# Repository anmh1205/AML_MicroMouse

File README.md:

# AML MicroMouse

An autonomous Micromouse robot built around an **STM32F407VET6** microcontroller and VL53L0X laser distance sensors, with firmware, PCB design files, maze-solving experiments, and simulator resources.

*Competition footage — [watch on YouTube](https://www.youtube.com/watch?v=a5xwwyJaq_M).*

## Project overview

In a Micromouse competition, a robot must explore an initially unknown maze, recognize walls, determine a route toward the goal, and execute that route accurately. This project brings together embedded sensing, motion control, route planning, custom electronics, and simulation in a single engineering workspace.

The repository includes STM32 firmware workspaces and supporting experiments rather than a single installation package. It also retains the hardware and simulation materials used during development.

## Technical scope

| Area | Repository contents |
| --- | --- |
| Controller | STM32F407VET6-based firmware project |
| Wall sensing | VL53L0X laser-ranging sensors |
| Firmware toolchain | STM32CubeIDE-compatible project metadata, STM32CubeMX `.ioc` configuration, and build files |
| Embedded software | Sensor acquisition, control code, and maze-navigation experiments |
| Simulation | Micromouse simulator materials and C examples |
| Electronics | PCB design assets and bill of materials |

## Exploring and building the firmware

Start with the STM32 project under `1. MicroMouse Code/0. MicroMouse - STM32F407VET6/PCB_V1`. That directory contains `.project`, `.cproject`, `PCB_V1.ioc`, source code, startup assembly, linker scripts, and other toolchain files.

For a first build:

1. Install an STM32 development toolchain compatible with the included project, such as STM32CubeIDE.
2. Import the `PCB_V1` project from the existing-project workflow.
3. Review the MCU configuration, compiler settings, external libraries, and selected build configuration.
4. Build for the intended hardware. Flash only after confirming connections, debugger settings, and motor safety.

Some directories contain generated `Debug/` or `build/` artifacts from earlier development. These are historical outputs, not evidence that the current project has been revalidated with recent toolchain versions.

## Repository guide

- [Examples](0.%20Example/) — source material and technical experiments.
- [Firmware and controller projects](1.%20MicroMouse%20Code/) — STM32 firmware, ESP32 remote experiments, and C tests.
- [PCB design](2.%20MicroMouse%20PCB/) — electronics project materials.
- [Mechanical drawings](4.%20Drawing/) — design and mechanical references.
- [Simulation resources](5.%20Simulator/) — Micromouse simulator and example code.
- [Bill of materials](Bill.xlsx) — component inventory reference.

## Development context

The repository captures the engineering process behind a competition robot, including intermediate experiments and physical design files. Several firmware and simulator resources coexist; they should not be assumed to represent one unified production release.

No repository-wide license is currently declared. Check the terms of bundled libraries and third-party simulator materials before reuse or redistribution.

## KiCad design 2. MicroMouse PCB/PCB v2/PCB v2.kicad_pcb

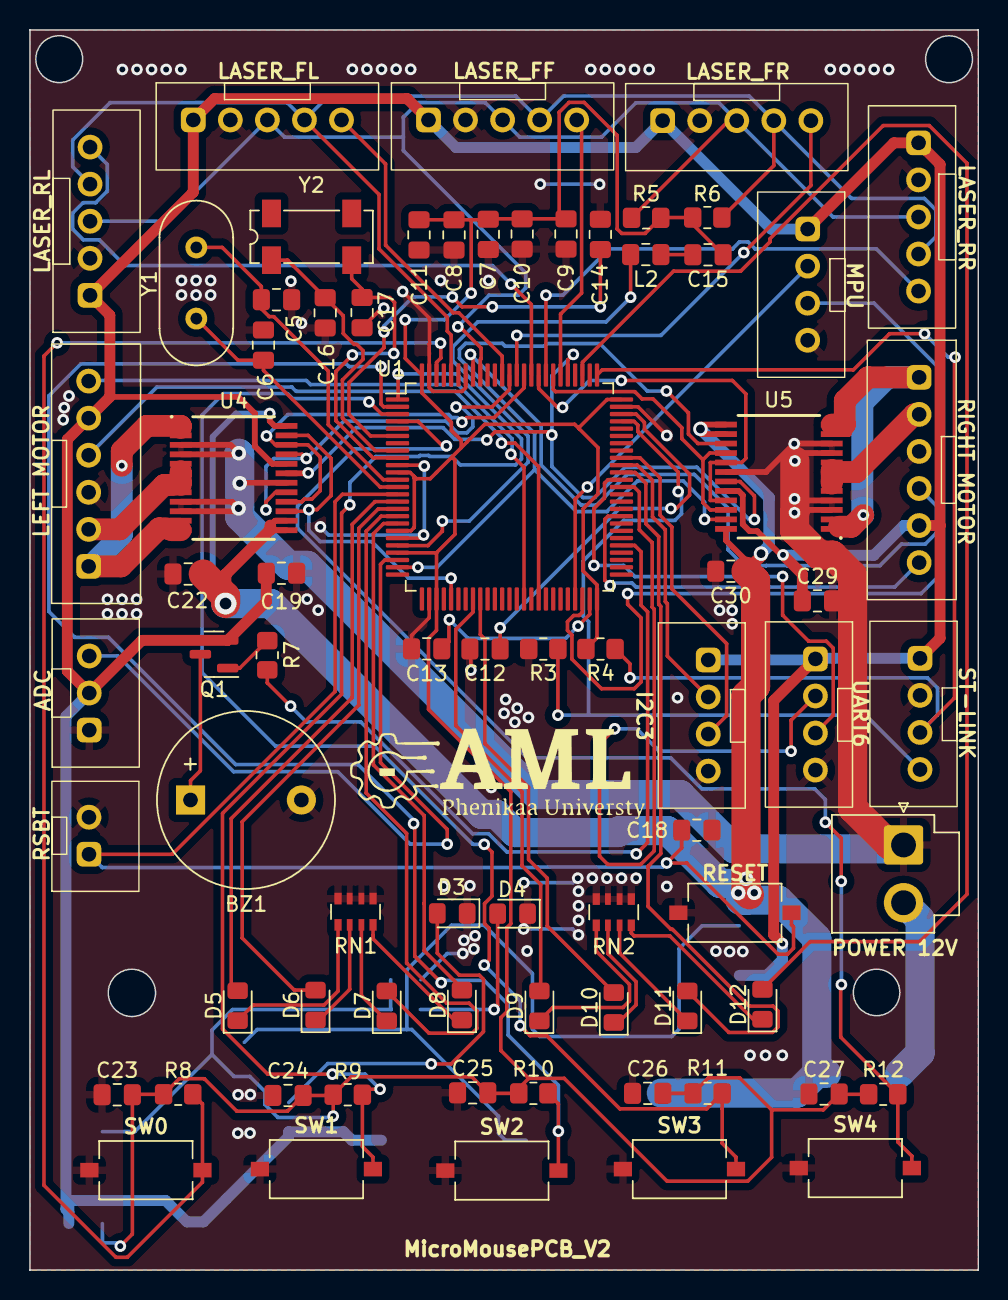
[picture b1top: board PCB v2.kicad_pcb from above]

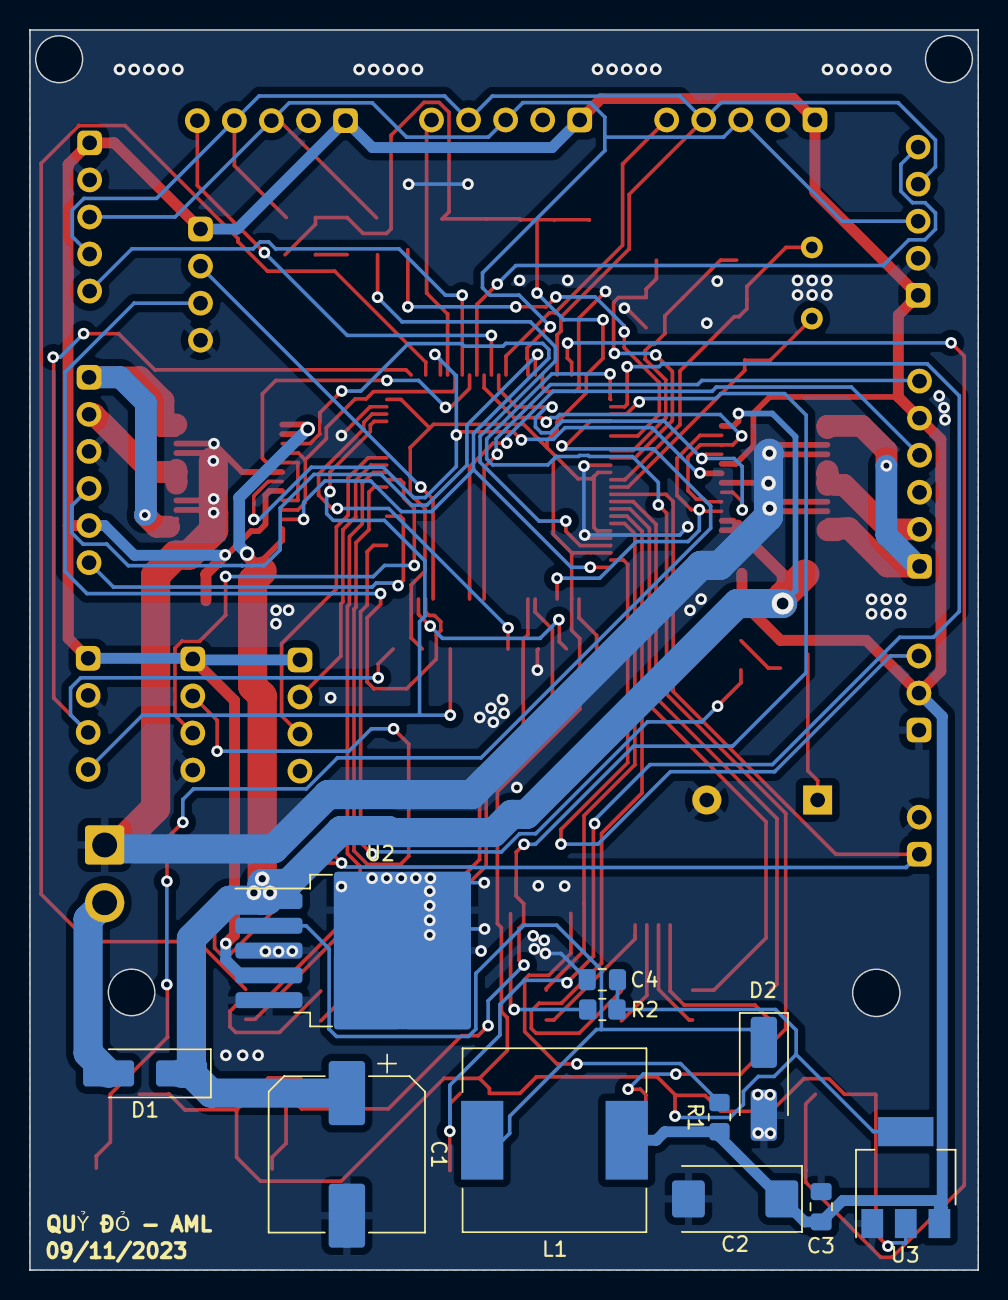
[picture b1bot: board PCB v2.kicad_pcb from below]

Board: 2 copper layers, 65.0 x 85.0 mm, 84 parts (11 on the bottom side), 73 nets.

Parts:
ADC: ADKEYBOARD; JST 3
BZ1: Buzzer; Buzzer_12x9.5RM7.6
C1: 680u; CP_Elec_10x10.5
C2: 220u; CP_EIA-7343-43_Kemet-X_Pad2.25x2.55mm_HandSolder
C3, C19, C22, C29, C30: 10U; C_0805_2012Metric_Pad1.18x1.45mm_HandSolder
C4: 47U; C_0805_2012Metric_Pad1.18x1.45mm_HandSolder
C5, C6, C16, C17: 20pF; C_0805_2012Metric_Pad1.18x1.45mm_HandSolder
C7, C8, C9, C10, C11, C12, C13, C14, C15, C18, C23, C24, C25, C26, C27: 100nF; C_0805_2012Metric_Pad1.18x1.45mm_HandSolder
D1, D2: 1N5822; D_SMA_Handsoldering
D3: 5VL; LED_0805_2012Metric_Pad1.15x1.40mm_HandSolder
D4, D5, D6, D7, D8, D9, D10, D11, D12: 3VL; LED_0805_2012Metric_Pad1.15x1.40mm_HandSolder
I2C3: I2C3; JST 4
L1: 33uH; L_12x12mm_H6mm
L2: 10uH; C_0805_2012Metric_Pad1.18x1.45mm_HandSolder
LASER_FF: FF; JST 5
LASER_FL: FL; JST 5
LASER_FR: FR; JST 5
LASER_RL: BL; JST 5
LASER_RR: BR; JST 5
LEFT MOTOR: LEFT_MOTOR; JST 6
MPU: MPU; JST 4
POWER 12V: Conn_01x02_Socket; JST_VH_B2P-VH_1x02_P3.96mm_Vertical
Q1: S8550; SOT-23
R1: 330; R_0805_2012Metric_Pad1.20x1.40mm_HandSolder
R2: 100; R_0805_2012Metric_Pad1.20x1.40mm_HandSolder
R3, R4: 10K; R_0805_2012Metric_Pad1.20x1.40mm_HandSolder
R5, R6: 4.7K; R_0805_2012Metric_Pad1.20x1.40mm_HandSolder
R7, R8, R9, R10, R11, R12: 1K; R_0805_2012Metric_Pad1.20x1.40mm_HandSolder
RESET: SW_Push; SW_Tactile_SPST_NO_Straight_CK_PTS636Sx25SMTRLFS
RIGHT MOTOR: RIGHT_MOTOR; JST 6
RN1, RN2: R_Pack04; R_Array_Convex_4x0603
RSBT: Conn_01x02_Socket; JST 2
ST-LINK: STLINK; JST 4
SW0, SW1, SW2, SW3, SW4: SW_Push; SW_Tactile_SPST_NO_Straight_CK_PTS636Sx25SMTRLFS
U1: STM32F407VGTx; LQFP-100_14x14mm_P0.5mm
U2: LM2596S-5; TO-263-5_TabPin3
U3: AMS1117-3.3; SOT-223-3_TabPin2
U4, U5: TB6612FNG; SOP65P760X160-24N
UART6: UART6; JST 4
Y1: 25MHz; Crystal_HC49-U_Vertical
Y2: 32.768KHz; Crystal_SMD_SeikoEpson_MC306-4Pin_8.0x3.2mm

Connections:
+3.3V: C4.1, C7.1, C8.1, C9.1, C10.1, C11.1, C15.1, C23.2, C24.2, C25.2, C26.2, C27.2, R2.2, R4.2, R5.2, R6.2, R8.2, R9.2, R10.2, R11.2, R12.2, U1.11 (VDD), U1.19 (VDD), U1.22 (VDDA), U1.28 (VDD), U1.50 (VDD), U1.75 (VDD), U1.100 (VDD), U3.2 (VO)
+5V: ADC.2, C2.1, C3.1, C19.1, C29.1, I2C3.1, L1.2, LASER_FF.1, LASER_FL.1, LASER_FR.1, LASER_RL.1, LASER_RR.1, LEFT MOTOR.5, MPU.1, Q1.1 (E), R1.1, RIGHT MOTOR.5, ST-LINK.1, U2.4 (FB), U3.3 (VI), U4.20 (VCC), U5.20 (VCC), UART6.1
+12V: C1.1, C22.1, C30.1, D1.1 (K), U2.1 (VIN), U4.13 (VM2), U4.14 (VM3), U4.24 (VM1), U5.13 (VM2), U5.14 (VM3), U5.24 (VM1)
/ADC1: ADC.3, U1.23 (PA0)
/AIN1: U1.88 (PD7), U4.17 (BIN1), U4.21 (AIN1)
/AIN2: U1.86 (PD5), U4.16 (BIN2), U4.22 (AIN2)
/AO1: LEFT MOTOR.1, U4.1 (AO1), U4.2 (AO1), U4.11 (BO1), U4.12 (BO1)
/AO2: LEFT MOTOR.2, U4.5 (AO2), U4.6 (AO2), U4.7 (BO2), U4.8 (BO2)
/BIN1: U1.84 (PD3), U5.17 (BIN1), U5.21 (AIN1)
/BIN2: U1.82 (PD1), U5.16 (BIN2), U5.22 (AIN2)
/BO1: RIGHT MOTOR.1, U5.1 (AO1), U5.2 (AO1), U5.11 (BO1), U5.12 (BO1)
/BO2: RIGHT MOTOR.2, U5.5 (AO2), U5.6 (AO2), U5.7 (BO2), U5.8 (BO2)
/BUZZER: R7.1, U1.55 (PD8)
/NRST: C18.2, RESET.2, RSBT.1, U1.14 (NRST)
/PA8: I2C3.3, U1.67 (PA8)
/PB10: MPU.2, U1.47 (PB10)
/PB11: MPU.3, U1.48 (PB11)
/PC0: D5.2 (A), U1.15 (PC0)
/PC1: D6.2 (A), U1.16 (PC1)
/PC2: D7.2 (A), U1.17 (PC2)
/PC3: D8.2 (A), U1.18 (PC3)
/PC4: D9.2 (A), U1.33 (PC4)
/PC5: D10.2 (A), U1.34 (PC5)
/PC6: U1.63 (PC6), UART6.2
/PC7: U1.64 (PC7), UART6.3
/PC8: D11.2 (A), U1.65 (PC8)
/PC9: I2C3.2, U1.66 (PC9)
/PC10: D12.2 (A), U1.78 (PC10)
/PC14: C16.2, U1.8 (PC14), Y2.1
/PC15: C17.2, U1.9 (PC15), Y2.2
/PE1: R8.1, SW0.2, U1.98 (PE1)
/PE2: R9.1, SW1.2, U1.1 (PE2)
/PE3: R10.1, SW2.2, U1.2 (PE3)
/PE4: R11.1, SW3.2, U1.3 (PE4)
/PE5: R12.1, SW4.2, U1.4 (PE5)
/PH0: C5.2, U1.12 (PH0), Y1.1
/PH1: C6.2, U1.13 (PH1), Y1.2
/PWMA: U1.30 (PA5), U4.15 (PWMB), U4.23 (PWMA)
/PWMB: U1.24 (PA1), U5.15 (PWMB), U5.23 (PWMA)
/SCL: LASER_FF.3, LASER_FL.3, LASER_FR.3, LASER_RL.3, LASER_RR.3, R5.1, U1.92 (PB6)
/SDA: LASER_FF.4, LASER_FL.4, LASER_FR.4, LASER_RL.4, LASER_RR.4, R6.1, U1.96 (PB9)
/STBY: U1.80 (PC12), U4.19 (STBY), U5.19 (STBY)
/SWCLK: R4.1, ST-LINK.3, U1.76 (PA14)
/SWDIO: R3.1, ST-LINK.4, U1.72 (PA13)
/TIM1_CH1: LEFT MOTOR.6, U1.40 (PE9)
/TIM1_CH2: LEFT MOTOR.4, U1.42 (PE11)
/TIM4_CH1: RIGHT MOTOR.6, U1.59 (PD12)
/TIM4_CH2: RIGHT MOTOR.4, U1.93 (PB7)
/XSHUT_BL: LASER_RL.5, U1.85 (PD4)
/XSHUT_BR: LASER_RR.5, U1.83 (PD2)
/XSHUT_FF: LASER_FF.5, U1.81 (PD0)
/XSHUT_FL: LASER_FL.5, U1.89 (PB3)
/XSHUT_FR: LASER_FR.5, U1.87 (PD6)
GND: ADC.1, BZ1.2 (+), C1.2, C2.2, C3.2, C4.2, C5.1, C6.1, C7.2, C8.2, C9.2, C10.2, C11.2, C12.1, C13.1, C14.1, C16.1, C17.1, C18.1, C19.2, C22.2, C23.1, C24.1, C25.1, C26.1, C27.1, C29.2, C30.2, D2.2 (A), D3.1 (K), D4.1 (K), I2C3.4, LASER_FF.2, LASER_FL.2, LASER_FR.2, LASER_RL.2, LASER_RR.2, LEFT MOTOR.3, MPU.4, POWER 12V.1, R3.2, RESET.1, RIGHT MOTOR.3, RN1.5 (R4.2), RN1.6 (R3.2), RN1.7 (R2.2), RN1.8 (R1.2), RN2.5 (R4.2), RN2.6 (R3.2), RN2.7 (R2.2), RN2.8 (R1.2), RSBT.2, ST-LINK.2, SW0.1, SW1.1, SW2.1, SW3.1, SW4.1, U1.10 (VSS), U1.20 (VSSA), U1.27 (VSS), U1.74 (VSS), U1.94 (BOOT0), U1.99 (VSS), U2.3 (GND), U2.5 (~ON/OFF), U3.1 (GND), U4.3 (PGND1), U4.4 (PGND1), U4.9 (PGND2), U4.10 (PGND2), U4.18 (GND), U5.3 (PGND1), U5.4 (PGND1), U5.9 (PGND2), U5.10 (PGND2), U5.18 (GND), UART6.4
unnamed: BZ1.1 (-), Q1.3 (C)
unnamed: C15.2, L2.1
unnamed: D1.2 (A), POWER 12V.2
unnamed: D2.1 (K), L1.1, U2.2 (OUT)
unnamed: D3.2 (A), R1.2
unnamed: D4.2 (A), R2.1
unnamed: D5.1 (K), RN1.1 (R1.1)
unnamed: D6.1 (K), RN1.2 (R2.1)
unnamed: D7.1 (K), RN1.3 (R3.1)
unnamed: D8.1 (K), RN1.4 (R4.1)
unnamed: D9.1 (K), RN2.1 (R1.1)
unnamed: D10.1 (K), RN2.2 (R2.1)
unnamed: D11.1 (K), RN2.3 (R3.1)
unnamed: D12.1 (K), RN2.4 (R4.1)
unnamed: Q1.2 (B), R7.2
unnamed: C14.2, U1.6 (VBAT)
unnamed: C13.2, U1.49 (VCAP_1)
unnamed: C12.2, U1.73 (VCAP_2)
unnamed: L2.2, U1.21 (VREF+)

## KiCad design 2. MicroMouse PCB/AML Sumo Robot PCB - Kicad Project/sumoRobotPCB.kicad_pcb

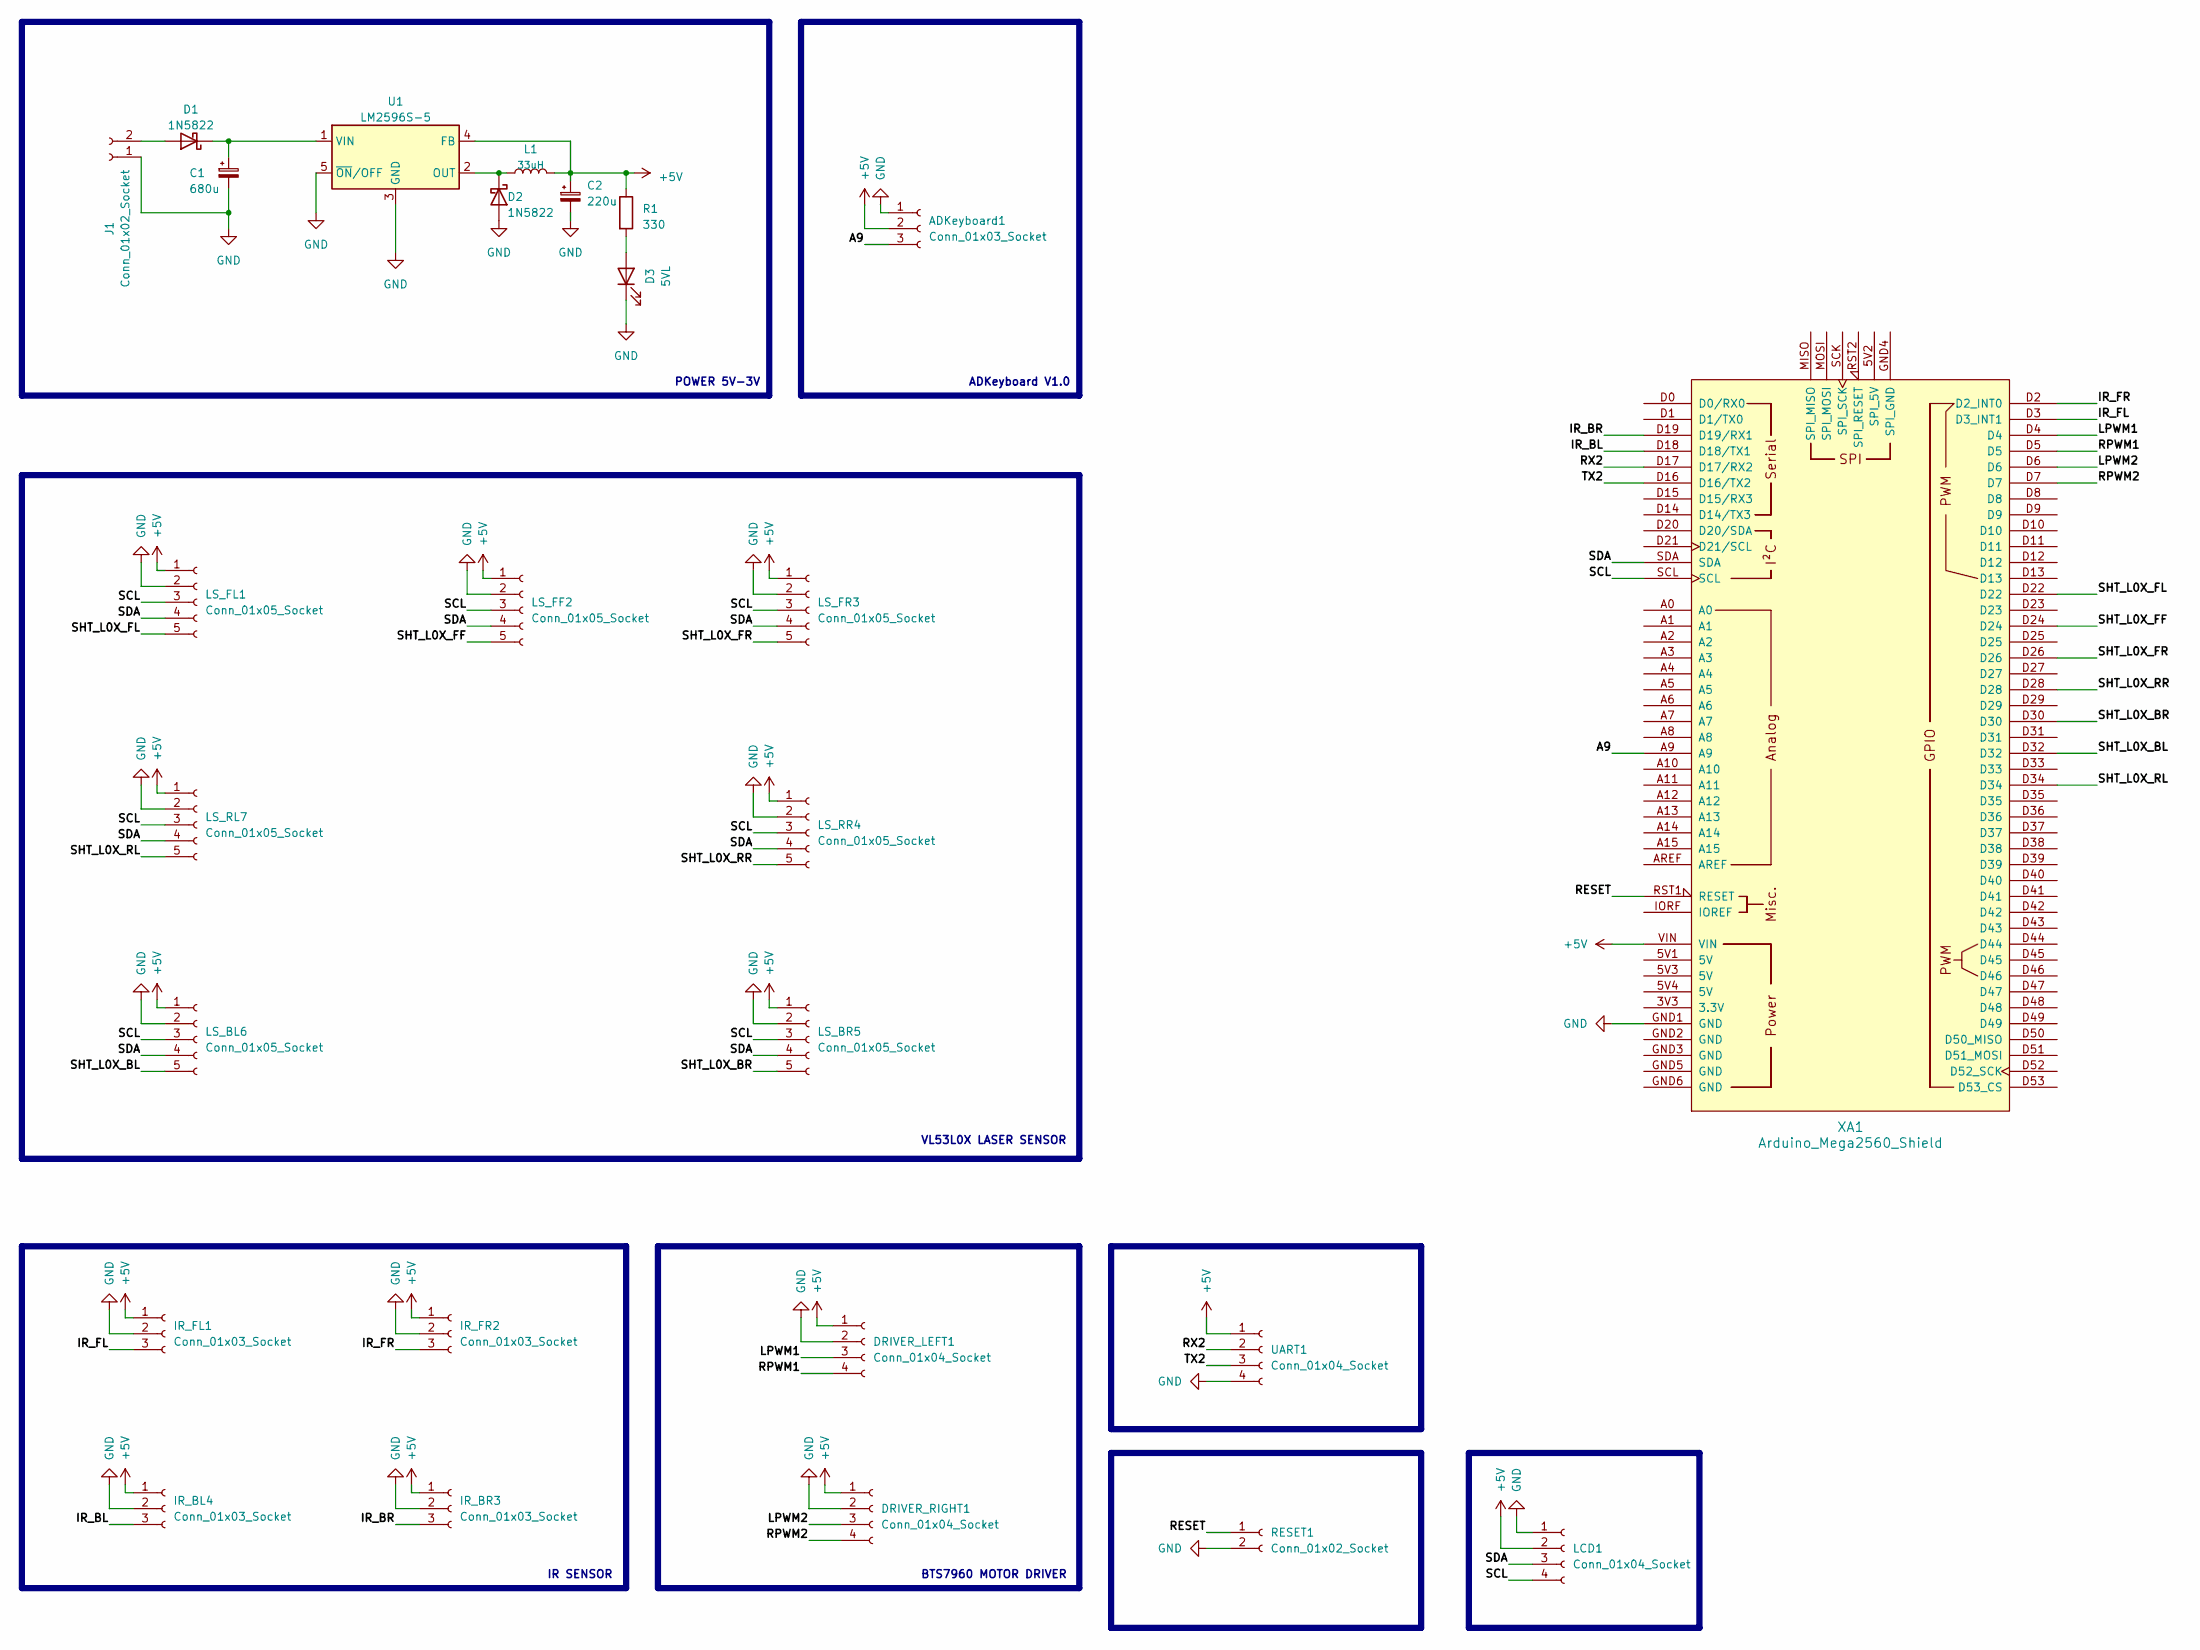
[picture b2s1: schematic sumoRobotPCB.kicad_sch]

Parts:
ADKeyboard1: Conn_01x03_Socket; JST_GH_BM03B-GHS-TBT_1x03-1MP_P1.25mm_Vertical
C1: 680u; CP_Elec_10x10.5
C2: 220u; CP_EIA-7343-43_Kemet-X_Pad2.25x2.55mm_HandSolder
D1, D2: 1N5822; D_SMA_Handsoldering
D3: 5VL; LED_0805_2012Metric_Pad1.15x1.40mm_HandSolder
DRIVER_LEFT1: Conn_01x04_Socket; JST_GH_BM04B-GHS-TBT_1x04-1MP_P1.25mm_Vertical
DRIVER_RIGHT1: Conn_01x04_Socket; JST_GH_BM04B-GHS-TBT_1x04-1MP_P1.25mm_Vertical
IR_BL4: Conn_01x03_Socket; JST_GH_BM03B-GHS-TBT_1x03-1MP_P1.25mm_Vertical
IR_BR3: Conn_01x03_Socket; JST_GH_BM03B-GHS-TBT_1x03-1MP_P1.25mm_Vertical
IR_FL1: Conn_01x03_Socket; JST_GH_BM03B-GHS-TBT_1x03-1MP_P1.25mm_Vertical
IR_FR2: Conn_01x03_Socket; JST_GH_BM03B-GHS-TBT_1x03-1MP_P1.25mm_Vertical
J1: Conn_01x02_Socket; JST_VH_B2P-VH_1x02_P3.96mm_Vertical
L1: 33uH; L_12x12mm_H6mm
LCD1: Conn_01x04_Socket; JST_GH_BM04B-GHS-TBT_1x04-1MP_P1.25mm_Vertical
LS_BL6: Conn_01x05_Socket; JST_GH_BM05B-GHS-TBT_1x05-1MP_P1.25mm_Vertical
LS_BR5: Conn_01x05_Socket; JST_GH_BM05B-GHS-TBT_1x05-1MP_P1.25mm_Vertical
LS_FF2: Conn_01x05_Socket; JST_GH_BM05B-GHS-TBT_1x05-1MP_P1.25mm_Vertical
LS_FL1: Conn_01x05_Socket; JST_GH_BM05B-GHS-TBT_1x05-1MP_P1.25mm_Vertical
LS_FR3: Conn_01x05_Socket; JST_GH_BM05B-GHS-TBT_1x05-1MP_P1.25mm_Vertical
LS_RL7: Conn_01x05_Socket; JST_GH_BM05B-GHS-TBT_1x05-1MP_P1.25mm_Vertical
LS_RR4: Conn_01x05_Socket; JST_GH_BM05B-GHS-TBT_1x05-1MP_P1.25mm_Vertical
R1: 330; R_0805_2012Metric_Pad1.20x1.40mm_HandSolder
RESET1: Conn_01x02_Socket; JST_GH_BM02B-GHS-TBT_1x02-1MP_P1.25mm_Vertical
U1: LM2596S-5; TO-263-5_TabPin3
UART1: Conn_01x04_Socket; JST_GH_BM04B-GHS-TBT_1x04-1MP_P1.25mm_Vertical
XA1: Arduino_Mega2560_Shield

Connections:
+5V: ADKeyboard1.2, C2.1, DRIVER_LEFT1.1, DRIVER_RIGHT1.1, IR_BL4.1, IR_BR3.1, IR_FL1.1, IR_FR2.1, L1.2, LCD1.2, LS_BL6.1, LS_BR5.1, LS_FF2.1, LS_FL1.1, LS_FR3.1, LS_RL7.1, LS_RR4.1, R1.1, U1.4 (FB), UART1.1, XA1.VIN
/A9: ADKeyboard1.3, XA1.A9
/IR_BL: IR_BL4.3, XA1.D18 (D18/TX1)
/IR_BR: IR_BR3.3, XA1.D19 (D19/RX1)
/IR_FL: IR_FL1.3, XA1.D3 (D3_INT1)
/IR_FR: IR_FR2.3, XA1.D2 (D2_INT0)
/LPWM1: DRIVER_LEFT1.3, XA1.D4
/LPWM2: DRIVER_RIGHT1.3, XA1.D6
/RESET: RESET1.1, XA1.RST1 (RESET)
/RPWM1: DRIVER_LEFT1.4, XA1.D5
/RPWM2: DRIVER_RIGHT1.4, XA1.D7
/RX2: UART1.2, XA1.D17 (D17/RX2)
/SCL: LCD1.4, LS_BL6.3, LS_BR5.3, LS_FF2.3, LS_FL1.3, LS_FR3.3, LS_RL7.3, LS_RR4.3, XA1.SCL
/SDA: LCD1.3, LS_BL6.4, LS_BR5.4, LS_FF2.4, LS_FL1.4, LS_FR3.4, LS_RL7.4, LS_RR4.4, XA1.SDA
/SHT_L0X_BL: LS_BL6.5, XA1.D32
/SHT_L0X_BR: LS_BR5.5, XA1.D30
/SHT_L0X_FF: LS_FF2.5, XA1.D24
/SHT_L0X_FL: LS_FL1.5, XA1.D22
/SHT_L0X_FR: LS_FR3.5, XA1.D26
/SHT_L0X_RL: LS_RL7.5, XA1.D34
/SHT_L0X_RR: LS_RR4.5, XA1.D28
/TX2: UART1.3, XA1.D16 (D16/TX2)
GND: ADKeyboard1.1, C1.2, C2.2, D2.2 (A), D3.1 (K), DRIVER_LEFT1.2, DRIVER_RIGHT1.2, IR_BL4.2, IR_BR3.2, IR_FL1.2, IR_FR2.2, J1.1, LCD1.1, LS_BL6.2, LS_BR5.2, LS_FF2.2, LS_FL1.2, LS_FR3.2, LS_RL7.2, LS_RR4.2, RESET1.2, U1.3 (GND), U1.5 (~ON/OFF), UART1.4, XA1.GND1 (GND)
unnamed: D1.2 (A), J1.2
unnamed: C1.1, D1.1 (K), U1.1 (VIN)
unnamed: D2.1 (K), L1.1, U1.2 (OUT)
unnamed: D3.2 (A), R1.2

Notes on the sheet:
BTS7960 MOTOR DRIVER
ADKeyboard V1.0
VL53L0X LASER SENSOR
IR SENSOR
POWER 5V-3V

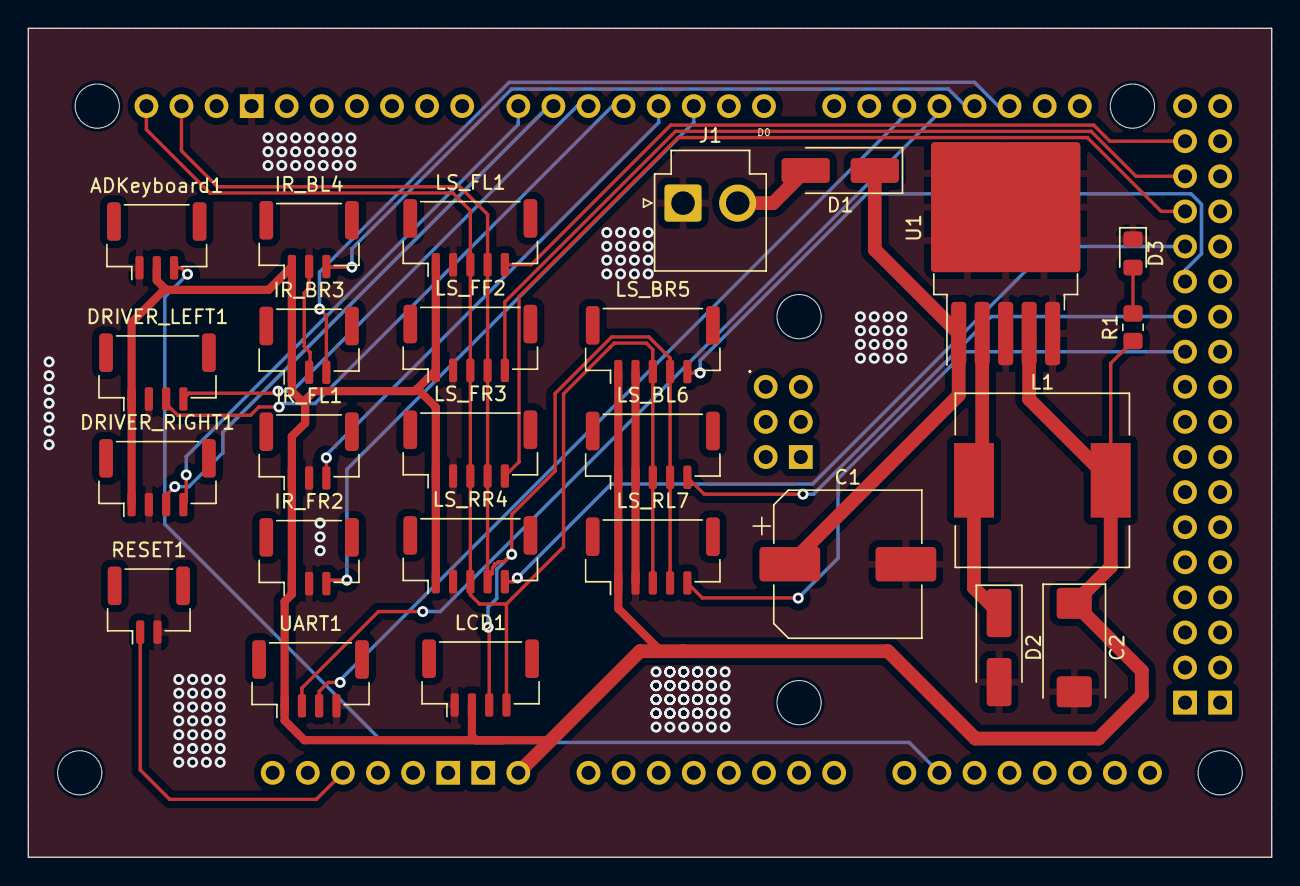
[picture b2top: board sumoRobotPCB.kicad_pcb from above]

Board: 2 copper layers, 90.0 x 60.0 mm, 27 parts (0 on the bottom side), 27 nets.

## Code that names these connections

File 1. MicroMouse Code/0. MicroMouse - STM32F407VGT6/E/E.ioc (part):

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Mcu.Name=STM32F407V(E-G)Tx
Mcu.Package=LQFP100
Mcu.UserName=STM32F407VGTx
PA0-WKUP.GPIOParameters=GPIO_PuPd
PA0-WKUP.GPIO_PuPd=GPIO_PULLDOWN
PA0-WKUP.Signal=GPIO_Input
PA1.Signal=S_TIM2_CH2
PA13.Mode=Serial_Wire
PA13.Signal=SYS_JTMS-SWDIO
PA14.Mode=Serial_Wire
PA14.Signal=SYS_JTCK-SWCLK
PA5.Signal=S_TIM2_CH1_ETR
PA8.Mode=I2C
PA8.Signal=I2C3_SCL
PB10.Mode=Asynchronous
PB10.Signal=USART3_TX
PB11.Mode=Asynchronous
PB11.Signal=USART3_RX
PB3.GPIOParameters=GPIO_Label
PB3.GPIO_Label=XSHUT_FL
PB3.Signal=GPIO_Output
PB6.Mode=I2C
PB6.Signal=I2C1_SCL
PB7.Signal=S_TIM4_CH2
PB9.Mode=I2C
PB9.Signal=I2C1_SDA
PC0.Signal=GPIO_Output
PC1.Signal=GPIO_Output
PC10.Signal=GPIO_Output
PC12.GPIOParameters=GPIO_Label
PC12.GPIO_Label=STBY
PC12.Signal=GPIO_Output
PC14-OSC32_IN.Mode=LSE-External-Oscillator
PC14-OSC32_IN.Signal=RCC_OSC32_IN
PC15-OSC32_OUT.Mode=LSE-External-Oscillator
PC15-OSC32_OUT.Signal=RCC_OSC32_OUT
PC2.Signal=GPIO_Output
PC3.Signal=GPIO_Output
PC4.Signal=GPIO_Output
PC5.Signal=GPIO_Output
PC6.Mode=Asynchronous
PC6.Signal=USART6_TX
PC7.Mode=Asynchronous
PC7.Signal=USART6_RX
PC8.Signal=GPIO_Output
PC9.Mode=I2C
PC9.Signal=I2C3_SDA
PD0.GPIOParameters=GPIO_Label
PD0.GPIO_Label=XSHUT_BL
PD0.Signal=GPIO_Output
PD1.GPIOParameters=GPIO_Label
PD1.GPIO_Label=BIN2
PD1.Signal=GPIO_Output
PD12.Signal=S_TIM4_CH1
PD13.Signal=GPIO_Output
PD2.GPIOParameters=GPIO_Label
PD2.GPIO_Label=XSHUT_BR
PD2.Signal=GPIO_Output
PD3.GPIOParameters=GPIO_Label
PD3.GPIO_Label=BIN1
PD3.Signal=GPIO_Output
PD4.GPIOParameters=GPIO_Label
PD4.GPIO_Label=XSHUT_FR
PD4.Signal=GPIO_Output
PD5.GPIOParameters=GPIO_Label
PD5.GPIO_Label=AIN2
PD5.Signal=GPIO_Output
PD6.GPIOParameters=GPIO_Label
PD6.GPIO_Label=XSHUT_FF
PD6.Signal=GPIO_Output
PD7.GPIOParameters=GPIO_Label
PD7.GPIO_Label=AIN1
PD7.Signal=GPIO_Output
PD8.GPIOParameters=GPIO_PuPd,GPIO_Label,GPIO_ModeDefaultOutputPP
PD8.GPIO_Label=BUZZER
PD8.GPIO_ModeDefaultOutputPP=GPIO_MODE_OUTPUT_OD
PD8.GPIO_PuPd=GPIO_NOPULL
PD8.Signal=GPIO_Output
PE11.Signal=S_TIM1_CH2
PE9.Signal=S_TIM1_CH1
PH0-OSC_IN.Mode=HSE-External-Oscillator
PH0-OSC_IN.Signal=RCC_OSC_IN
PH1-OSC_OUT.Mode=HSE-External-Oscillator
PH1-OSC_OUT.Signal=RCC_OSC_OUT
RCC.HSE_VALUE=8000000
RCC.SYSCLKFreq_VALUE=168000000
RCC.SYSCLKSource=RCC_SYSCLKSOURCE_PLLCLK
board=custom

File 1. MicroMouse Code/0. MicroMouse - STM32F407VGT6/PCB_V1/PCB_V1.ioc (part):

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Mcu.Name=STM32F407V(E-G)Tx
Mcu.Package=LQFP100
Mcu.UserName=STM32F407VETx
PA1.Signal=S_TIM2_CH2
PA13.Mode=Serial_Wire
PA13.Signal=SYS_JTMS-SWDIO
PA14.Mode=Serial_Wire
PA14.Signal=SYS_JTCK-SWCLK
PA5.Signal=S_TIM2_CH1_ETR
PB10.GPIOParameters=GPIO_PuPd
PB10.GPIO_PuPd=GPIO_PULLUP
PB10.Mode=Asynchronous
PB10.Signal=USART3_TX
PB11.GPIOParameters=GPIO_PuPd
PB11.GPIO_PuPd=GPIO_PULLUP
PB11.Mode=Asynchronous
PB11.Signal=USART3_RX
PB3.GPIOParameters=GPIO_Label
PB3.GPIO_Label=XSHUT_FL
PB3.Signal=GPIO_Output
PB6.GPIOParameters=GPIO_Pu
PB6.GPIO_Pu=GPIO_NOPULL
PB6.Mode=I2C
PB6.Signal=I2C1_SCL
PB7.Signal=S_TIM4_CH2
PB9.GPIOParameters=GPIO_Pu
PB9.GPIO_Pu=GPIO_NOPULL
PB9.Mode=I2C
PB9.Signal=I2C1_SDA
PC0.Signal=GPIO_Output
PC1.Signal=GPIO_Output
PC10.Signal=GPIO_Output
PC12.GPIOParameters=GPIO_Label
PC12.GPIO_Label=STBY
PC12.Signal=GPIO_Output
PC2.Signal=GPIO_Output
PC3.Signal=GPIO_Output
PC4.Signal=GPIO_Output
PC5.Signal=GPIO_Output
PC6.Mode=Asynchronous
PC6.Signal=USART6_TX
PC7.Mode=Asynchronous
PC7.Signal=USART6_RX
PC8.Signal=GPIO_Output
PD0.GPIOParameters=GPIO_Label
PD0.GPIO_Label=XSHUT_FF
PD0.Signal=GPIO_Output
PD1.GPIOParameters=GPIO_Label
PD1.GPIO_Label=BIN2
PD1.Signal=GPIO_Output
PD12.Signal=S_TIM4_CH1
PD13.Signal=GPIO_Output
PD2.GPIOParameters=GPIO_Label
PD2.GPIO_Label=XSHUT_BR
PD2.Signal=GPIO_Output
PD3.GPIOParameters=GPIO_Label
PD3.GPIO_Label=BIN1
PD3.Signal=GPIO_Output
PD4.GPIOParameters=GPIO_Label
PD4.GPIO_Label=XSHUT_BL
PD4.Signal=GPIO_Output
PD5.GPIOParameters=GPIO_Label
PD5.GPIO_Label=AIN2
PD5.Signal=GPIO_Output
PD6.GPIOParameters=GPIO_Label
PD6.GPIO_Label=XSHUT_FR
PD6.Signal=GPIO_Output
PD7.GPIOParameters=GPIO_Label
PD7.GPIO_Label=AIN1
PD7.Signal=GPIO_Output
PD8.GPIOParameters=PinState,GPIO_PuPd,GPIO_Label,GPIO_ModeDefaultOutputPP
PD8.GPIO_Label=BUZZER
PD8.GPIO_ModeDefaultOutputPP=GPIO_MODE_OUTPUT_OD
PD8.GPIO_PuPd=GPIO_NOPULL
PD8.PinState=GPIO_PIN_SET
PD8.Signal=GPIO_Output
PE1.Signal=GPXTI1
PE11.Signal=S_TIM1_CH2
PE2.Signal=GPXTI2
PE3.Signal=GPXTI3
PE4.Signal=GPXTI4
PE5.Signal=GPXTI5
PE9.Signal=S_TIM1_CH1
PH0-OSC_IN.Mode=HSE-External-Oscillator
PH0-OSC_IN.Signal=RCC_OSC_IN
PH1-OSC_OUT.Mode=HSE-External-Oscillator
PH1-OSC_OUT.Signal=RCC_OSC_OUT
RCC.HSE_VALUE=25000000
RCC.SYSCLKFreq_VALUE=168000000
RCC.SYSCLKSource=RCC_SYSCLKSOURCE_PLLCLK
board=custom

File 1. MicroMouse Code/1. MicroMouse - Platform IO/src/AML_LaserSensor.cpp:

/*
  Library for 7 VL53L0x sensor

  Last updated: 11PM 13/06/2023 UTC+7
  Authors: anmh1205

*/

#include <AML_LaserSensor.h>

// Khởi tạo theo thư viện
VL53L0X FL;
VL53L0X FF;
VL53L0X FR;
VL53L0X RR;
VL53L0X BR;
VL53L0X BL;
VL53L0X RL;

// set the pins to shutdown for all 7 sensors

#define SHT_L0X_FL 22 // XSHUT Pin laser 1
#define SHT_L0X_FF 24 // XSHUT Pin laser 2
#define SHT_L0X_FR 26 // XSHUT Pin laser 3
#define SHT_L0X_RR 28 // XSHUT Pin laser 4
#define SHT_L0X_BR 30 // XSHUT Pin laser 5
#define SHT_L0X_BL 32 // XSHUT Pin laser 6
#define SHT_L0X_RL 34 // XSHUT Pin laser 7

// address we will assign for all 7 sensor

#define L0X_FL_ADDRESS 0x28
#define L0X_FF_ADDRESS 0x30
#define L0X_FR_ADDRESS 0x31
#define L0X_RR_ADDRESS 0x32
#define L0X_BR_ADDRESS 0x33
#define L0X_BL_ADDRESS 0x34
#define L0X_RL_ADDRESS 0x35

// Mảng giá trị cảm biến
int AML_laserSensorValue[8];

// bật từng laser lên để cài địa chỉ bằng chân XSHUT
void AML_LaserSensor_setup()
{
  pinMode(SHT_L0X_FL, OUTPUT);
  pinMode(SHT_L0X_FF, OUTPUT);
  pinMode(SHT_L0X_FR, OUTPUT);
  pinMode(SHT_L0X_RR, OUTPUT);
  pinMode(SHT_L0X_BR, OUTPUT);
  pinMode(SHT_L0X_BL, OUTPUT);
  pinMode(SHT_L0X_RL, OUTPUT);

  Serial.println(0);
  // Serial.println("Shutdown pins inited...");

  digitalWrite(SHT_L0X_FL, LOW);
  digitalWrite(SHT_L0X_FF, LOW);
  digitalWrite(SHT_L0X_FR, LOW);
  digitalWrite(SHT_L0X_RR, LOW);
  digitalWrite(SHT_L0X_BR, LOW);
  digitalWrite(SHT_L0X_BL, LOW);
  digitalWrite(SHT_L0X_RL, LOW);

  Serial.println(1);

  // all unreset
  digitalWrite(SHT_L0X_FL, HIGH);
  digitalWrite(SHT_L0X_FF, HIGH);
  digitalWrite(SHT_L0X_FR, HIGH);
  digitalWrite(SHT_L0X_RR, HIGH);
  digitalWrite(SHT_L0X_BR, HIGH);
  digitalWrite(SHT_L0X_BL, HIGH);
  digitalWrite(SHT_L0X_RL, HIGH);
  delay(10);

  Serial.println(2);

  // activating L0X_L and reseting L0X_F
  digitalWrite(SHT_L0X_FL, HIGH);
  digitalWrite(SHT_L0X_FF, LOW);
  digitalWrite(SHT_L0X_FR, LOW);
  digitalWrite(SHT_L0X_RR, LOW);
  digitalWrite(SHT_L0X_BR, LOW);
  digitalWrite(SHT_L0X_BL, LOW);
  digitalWrite(SHT_L0X_RL, LOW);

  Serial.println(3);

  delay(10);
  FL.setAddress(L0X_FL_ADDRESS);

  Serial.println(4);

  digitalWrite(SHT_L0X_FF, HIGH);
  delay(10);
  FF.setAddress(L0X_FF_ADDRESS);

  Serial.println(5);

  digitalWrite(SHT_L0X_FR, HIGH);
  delay(10);
  FR.setAddress(L0X_FR_ADDRESS);

  Serial.println(6);

  digitalWrite(SHT_L0X_RR, HIGH);
  delay(10);
  RR.setAddress(L0X_RR_ADDRESS);

  Serial.println(7);

  digitalWrite(SHT_L0X_BR, HIGH);
  delay(10);
  BR.setAddress(L0X_BR_ADDRESS);

  Serial.println(8);

  digitalWrite(SHT_L0X_BL, HIGH);
  delay(10);
  BL.setAddress(L0X_BL_ADDRESS);

  Serial.println(9);

  digitalWrite(SHT_L0X_RL, HIGH);
  delay(10);
  RL.setAddress(L0X_RL_ADDRESS);

  Serial.println(10);

  delay(10);

  FL.init();
  FF.init();
  FR.init();
  RR.init();
  BR.init();
  BL.init();
  RL.init();

  Serial.println(11);

  // Gắn cờ lỗi
  FL.setTimeout(500);
  FF.setTimeout(500);
  FR.setTimeout(500);
  RR.setTimeout(500);
  BR.setTimeout(500);
  BL.setTimeout(500);
  RL.setTimeout(500);

  Serial.println(12);

  // // reduce timing budget to 10 ms (default is about 33 ms)
  FL.setMeasurementTimingBudget(10);
  FF.setMeasurementTimingBudget(10);
  FR.setMeasurementTimingBudget(10);
  RR.setMeasurementTimingBudget(10);
  BR.setMeasurementTimingBudget(10);
  BL.setMeasurementTimingBudget(10);
  RL.setMeasurementTimingBudget(10);

  FF.startContinuous();
  FR.startContinuous();
  RR.startContinuous();
  BR.startContinuous();
  BL.startContinuous();
  RL.startContinuous();
  FL.startContinuous();

  Serial.println("Laser sensor inited...");
}

// Đọc cảm biến có số thứ tự là số truyền vào hàm
float AML_LaserSensor_readSingle(int laserNumber)
{
  AML_LaserSensor_readAll(AML_laserSensorValue);
  return AML_laserSensorValue[laserNumber];
}


// Đọc laser (không ghi ra serial)
void AML_LaserSensor_readAll(int *userArrayAddress)
{
  *(userArrayAddress + 0) = FL.readRangeContinuousMillimeters();

  *(userArrayAddress + 1) = FF.readRangeContinuousMillimeters();

  *(userArrayAddress + 2) = FR.readRangeContinuousMillimeters();

  *(userArrayAddress + 3) = RR.readRangeContinuousMillimeters();

  *(userArrayAddress + 4) = BR.readRangeContinuousMillimeters();

  *(userArrayAddress + 5) = BL.readRangeContinuousMillimeters();

  *(userArrayAddress + 6) = RL.readRangeContinuousMillimeters();
}

// Hàm này giống hệt readLaserSensor(), khác mỗi cái có ghi ra serial để xem giá trị
void AML_LaserSensor_readAllTest(int *userArrayAddress)
{
  *(userArrayAddress + 0) = FL.readRangeContinuousMillimeters();
  Serial.print(AML_laserSensorValue[0]);

  Serial.print("   ");

  *(userArrayAddress + 1) = FF.readRangeContinuousMillimeters();
  Serial.print(AML_laserSensorValue[1]);

  Serial.print("   ");

  *(userArrayAddress + 2) = FR.readRangeContinuousMillimeters();
  Serial.print(AML_laserSensorValue[2]);

  Serial.print("   ");

  *(userArrayAddress + 3) = RR.readRangeContinuousMillimeters();
  Serial.print(AML_laserSensorValue[3]);

  Serial.print("   ");

  *(userArrayAddress + 4) = BR.readRangeContinuousMillimeters();
  Serial.print(AML_laserSensorValue[4]);

  Serial.print("   ");

  *(userArrayAddress + 5) = BL.readRangeContinuousMillimeters();
  Serial.print(AML_laserSensorValue[5]);

  Serial.print("   ");

  *(userArrayAddress + 6) = RL.readRangeContinuousMillimeters();
  Serial.print(AML_laserSensorValue[6]);

  Serial.println("   ");
}

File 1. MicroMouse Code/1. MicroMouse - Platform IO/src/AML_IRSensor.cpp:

/*
  IR sensor library for emergency escape

  Last updated: 10AM 14/06/2023 UTC+7
  Authors: anmh1205

*/

#include <AML_IRSensor.h>

const int IR_FL = 3;
const int IR_FR = 2;
const int IR_BR = 19;
const int IR_BL = 18;

volatile boolean flagInterrupt[4] = {false, false, false, false};
volatile unsigned long timer1 = 0;

// Wait for all interrupts to clear or timeout
void AML_IRSensor_standby()
{
  unsigned time = 700;

  while (millis() - timer1 < time && (flagInterrupt[0] || flagInterrupt[1] || flagInterrupt[2] || flagInterrupt[3]))
    ;

  // Reset all flags
  for (int i = 0; i < 4; i++)
    flagInterrupt[i] = false;
}

// Handle all interrupts
void InterruptHandler(int index, int pwmL, int pwmR)
{
  AML_MotorControl_PWM(pwmL, pwmR);
  flagInterrupt[index] = true;
  timer1 = millis();

  // Reset all flags except the current one
  for (int i = 0; i < 4; i++)
  {
    if (i != index)
      flagInterrupt[i] = false;
  }
}

// FrontLeft
void Interrupt_0() { InterruptHandler(0, -150, -150); }

// FrontRight
void Interrupt_1() { InterruptHandler(1, -150, -150); }

// BackLeft
void Interrupt_2() { InterruptHandler(2, 150, 150); }

// BackRight
void Interrupt_3() { InterruptHandler(3, 150, 150); }

// Set up interrupt handlers
void AML_IRSensor_setup()
{
  attachInterrupt(digitalPinToInterrupt(IR_FL), Interrupt_0, RISING);
  attachInterrupt(digitalPinToInterrupt(IR_FR), Interrupt_1, RISING);
  attachInterrupt(digitalPinToInterrupt(IR_BR), Interrupt_2, RISING);
  attachInterrupt(digitalPinToInterrupt(IR_BL), Interrupt_3, RISING);
}

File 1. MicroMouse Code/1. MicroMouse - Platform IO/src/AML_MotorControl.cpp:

/*
  Library for control 2 motor 

  Last updated: 11AM 14/06/2023 UTC+7
  Authors: anmh1205

*/


#include <AML_MotorControl.h>

Servo motorL;
Servo motorR;


#define LPWM1 4 // Chân kết nối đến chân IN1 của động cơ L
#define RPWM1 5 // Chân kết nối đến chân IN2 của động cơ L
#define LPWM2 6 // Chân kết nối đến chân IN3 của động cơ R
#define RPWM2 7 // Chân kết nối đến chân IN4 của động cơ R




// Hàm điều khiển động cơ với ESC. Nhận giá trị -100 đến 100, giá trị âm đi lùi, dương đi tiến
void AML_MotorControl_ESC(int speedL, int speedR)
{
  if (speedL < 0)
  {
    speedL = map(abs(speedL), 0, 100, 90, 0);
  }
  else if (speedL > 0)
  {
    speedL = map(speedL, 0, 100, 110, 180);
  }
  else if (speedL == 0)
  {
    speedL = 100;
  }

  if (speedR < 0)
  {
    speedR = map(abs(speedR), 0, 100, 90, 0);
  }
  else if (speedR > 0)
  {
    speedR = map(speedR, 0, 100, 110, 180);
  }
  else if (speedR == 0)
  {
    speedR = 100;
  }

  motorL.write(speedL);
  motorR.write(speedR);

  Serial.print(speedL);
  Serial.print("      ");
  Serial.println(speedR);
}

// Xuất xung điều khiển động cơ: Truyền giá trị dương đi tiến, giá trị âm đi lùi
void AML_MotorControl_PWM(int pwmL, int pwmR)
{
  if (pwmL > 0) // L tiến
  {
    analogWrite(LPWM1, pwmL);
    analogWrite(RPWM1, 0);
  }
  else if (pwmL < 0) // L lùi
  {
    analogWrite(LPWM1, 0);
    analogWrite(RPWM1, abs(pwmL));
  }
  else if (pwmL == 0) // L đứng yên
  {
    analogWrite(LPWM1, 0);
    analogWrite(RPWM1, 0);
  }

  if (pwmR > 0) // R tiến
  {
    analogWrite(LPWM2, pwmR);
    analogWrite(RPWM2, 0);
  }
  else if (pwmR < 0) // R lùi
  {
    analogWrite(LPWM2, 0);
    analogWrite(RPWM2, abs(pwmR));
  }
  else if (pwmR == 0) // R đứng yên
  {
    analogWrite(LPWM2, 0);
    analogWrite(RPWM2, 0);
  }
}


void AML_MotorControl_setupL298()
{
  pinMode(LPWM1, OUTPUT);
  pinMode(RPWM1, OUTPUT);
  pinMode(LPWM2, OUTPUT);
  pinMode(RPWM2, OUTPUT);
}

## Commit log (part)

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2023-10-05 mpu DMA - stm32
2023-10-10 add AML_MPUSensor and AML_LaserSensor
2023-10-11 update 5 laser sensor
2023-10-13 solve ADC vs UART DMA
2023-10-18 add AML_Encoder.h and AML_MotorControl.h
2023-10-18 fix PWM
2023-10-23 pcb complete
2023-10-24 add BOM file
2023-10-26 add PID speed and Bill file
2023-10-27 add pid position function
2023-10-30 fix laser sensor issue
2023-10-30 update before pull
2023-11-01 - add ESP32 for remove - add test code folder
2023-11-02 test
2023-11-09 PCB V2 completed
2023-11-12 add Kalman Filter for laser sensor
2023-11-14 commit before change VL53L0X API
2023-11-16 added drawing V1
2023-11-17 17/11/2023 try to aligned
2023-11-21 added PID for turning and solved hardfault
2023-11-24 done code, waiting for test
2023-11-27 27/11/2023
2023-11-28 added some function && completed Run() in main.c
2023-11-30 maze measure
2023-12-01 completed solve maze
2023-12-02 Test Maze V1 (ok)
2023-12-04 commit before change turning algorithm
2023-12-05 05/12/2023
2023-12-11 resolved conflict and uploaded the newest version
2023-12-13 added AML_PID library (using anti-windup algorithm)
2023-12-15 added auto remark algorithm
2023-12-16 optimize algorithm
2023-12-20 test maze BK 2
2023-12-22 test maze BK 3 (ok)
2023-12-29 competition version
2024-10-01 updated some functions in main.c
2024-10-01 updated Bill file
2024-12-12 new algorithm
2025-02-09 - removed warning - fixed some bug
